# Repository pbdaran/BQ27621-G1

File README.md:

# BQ27621 Arduino Library

This Arduino library provides a comprehensive interface for the Texas Instruments BQ27621-G1 battery fuel gauge IC, enabling easy integration with Arduino-based projects. The library supports all major features of the BQ27621-G1 as described in the Technical Reference Manual (SLUUAD4C, December 2013 - Revised August 2014).

## Features

- **Control Commands**: Manage device states (SEALED/UNSEALED, CONFIG UPDATE, SHUTDOWN, etc.).
- **Standard Commands**: Read battery parameters such as Temperature, Voltage, StateOfCharge, RemainingCapacity, and more.
- **Extended Commands**: Access and modify Operation Configuration, Design Capacity, and block data operations.
- **Data Memory Access**: Configure safety parameters, charge termination, SOC thresholds, sleep current, terminate voltage, and battery chemistry ID.
- **Battery Profile Selection**: Support for default (CHEM_ID 0x1202) and alternate chemistry profiles (0x1210 for 4.3V, 0x354 for 4.35V).
- **I2C Communication**: Robust functions for reading and writing word and block data over I2C.

## Requirements

- **Hardware**:
  - Arduino-compatible board with I2C support (e.g., Arduino Uno, Mega, etc.).
  - BQ27621-G1 battery fuel gauge IC connected via I2C (SDA, SCL, power lines).
- **Software**:
  - Arduino IDE (version 1.8.0 or later recommended).
  - Wire library (included with Arduino IDE).
- **Dependencies**: None beyond the standard Arduino Wire library.

## Installation

1. **Download the Library**:
   - Clone this repository or download the ZIP file.
   - Extract the `BQ27621` folder containing `BQ27621.h`, `BQ27621.cpp`, and the example sketch.

2. **Install the Library**:
   - Place the `BQ27621` folder in your Arduino `libraries` directory (typically `~/Arduino/libraries/`).
   - Restart the Arduino IDE if it was open during installation.

3. **Connect the Hardware**:
   - Connect the BQ27621-G1 to your Arduino:
     - SDA to Arduino SDA pin.
     - SCL to Arduino SCL pin.
     - VCC to 3.3V or 5V (check your board's compatibility).
     - GND to Arduino GND.
   - Verify the I2C address (default: 0x55). Adjust in the constructor if different.

4. **Open the Example**:
   - In the Arduino IDE, go to `File > Examples > BQ27621 > BQ27621_Example`.
   - Upload the example sketch to your Arduino.

## Usage

The library provides a `BQ27621` class with methods to interact with the fuel gauge. Below is a basic example of initializing the device and reading battery parameters:

```cpp
#include <Wire.h>
#include "BQ27621.h"

BQ27621 batteryGauge; // Default I2C address: 0x55

void setup() {
    Serial.begin(9600);
    while (!Serial);

    if (!batteryGauge.begin()) {
        Serial.println("Failed to initialize BQ27621!");
        while (1);
    }
    Serial.println("BQ27621 Initialized Successfully");

    // Configure battery parameters
    batteryGauge.setUnsealed();
    batteryGauge.enterConfigUpdate();
    batteryGauge.setDesignCapacity(1200); // Set to 1200mAh
    batteryGauge.setTerminateVoltage(3200); // Set to 3200mV
    batteryGauge.exitConfigUpdate();
    batteryGauge.setSealed();
}

void loop() {
    Serial.print("Voltage: ");
    Serial.print(batteryGauge.getVoltage());
    Serial.println(" mV");

    Serial.print("State of Charge: ");
    Serial.print(batteryGauge.getStateOfCharge());
    Serial.println(" %");

    Serial.print("Remaining Capacity: ");
    Serial.print(batteryGauge.getRemainingCapacity());
    Serial.println(" mAh");

    delay(5000); // Update every 5 seconds
}
```

## Example Sketch

The provided example sketch (`BQ27621_Example.ino`) demonstrates the full range of library features, including:

- Initializing the BQ27621-G1 and verifying communication.
- Configuring the device in UNSEALED mode.
- Setting safety parameters, charge termination, SOC thresholds, and operation configurations.
- Selecting an alternate battery chemistry profile (e.g., CHEM_ID 0x1210 for 4.3V batteries).
- Reading and displaying battery status (voltage, SOC, capacity, current, power, etc.).
- Toggling the GPOUT pin for debugging.

To use the example:
1. Open `BQ27621_Example.ino` in the Arduino IDE.
2. Adjust configuration parameters (e.g., DesignCapacity, TerminateVoltage) based on your battery specifications.
3. Upload the sketch and monitor the Serial output at 9600 baud.

## Library Methods

### Constructor
- `BQ27621(uint8_t i2cAddress = 0x55)`: Initialize with the I2C address (default: 0x55).

### Initialization
- `bool begin()`: Initialize I2C communication and verify device presence.

### Control Commands
- `uint16_t getControlStatus()`: Read the control status register.
- `void setBatteryInsert()`: Signal battery insertion.
- `void setBatteryRemove()`: Signal battery removal.
- `void enterShutdown()`: Enter SHUTDOWN mode.
- `void setSealed()`: Transition to SEALED mode.
- `void setUnsealed()`: Transition to UNSEALED mode (using default keys 0x8000 0x8000).
- `void toggleGPOUT()`: Pulse the GPOUT pin for 1ms.
- `void selectAltChem1()`: Select CHEM_ID 0x1210 (4.3V).
- `void selectAltChem2()`: Select CHEM_ID 0x354 (4.35V).
- `void enterConfigUpdate()`: Enter CONFIG UPDATE mode.
- `void exitConfigUpdate()`: Exit CONFIG UPDATE without OCV measurement.
- `void exitResim()`: Exit CONFIG UPDATE with resimulation.

### Standard Commands
- `uint16_t getTemperature()`: Read temperature in 0.1K.
- `void setTemperature(uint16_t temp)`: Set temperature (if OpConfig[TEMPS] = 1).
- `uint16_t getVoltage()`: Read cell voltage in mV.
- `uint16_t getFlags()`: Read status flags.
- `uint16_t getNominalAvailableCapacity()`: Read uncompensated capacity in mAh.
- `uint16_t getFullAvailableCapacity()`: Read uncompensated full capacity in mAh.
- `uint16_t getRemainingCapacity()`: Read compensated remaining capacity in mAh.
- `uint16_t getFullChargeCapacity()`: Read compensated full capacity in mAh.
- `int16_t getEffectiveCurrent()`: Read estimated current in mA.
- `int16_t getAveragePower()`: Read average power in mW.
- `uint16_t getStateOfCharge()`: Read state of charge in %.
- `uint16_t getInternalTemperature()`: Read internal temperature in 0.1K.
- `uint16_t getRemainingCapacityUnfiltered()`: Read unfiltered remaining capacity in mAh.
- `uint16_t getRemainingCapacityFiltered()`: Read filtered remaining capacity in mAh.
- `uint16_t getFullChargeCapacityUnfiltered()`: Read unfiltered full capacity in mAh.
- `uint16_t getFullChargeCapacityFiltered()`: Read filtered full capacity in mAh.
- `uint16_t getStateOfChargeUnfiltered()`: Read unfiltered state of charge in %.

### Extended Commands
- `uint16_t getOpConfig()`: Read operation configuration.
- `uint16_t getDesignCapacity()`: Read design capacity in mAh.
- `void setDesignCapacity(uint16_t capacity)`: Set design capacity.
- `uint8_t getBlockDataChecksum()`: Read block data checksum.
- `void setBlockDataChecksum(uint8_t checksum)`: Set block data checksum.
- `void setBlockDataControl(uint8_t value)`: Control data access mode.
- `void selectDataClass(uint8_t classId)`: Select data memory class.
- `void selectDataBlock(uint8_t blockId)`: Select data block.
- `void writeBlockData(uint8_t offset, uint8_t* data, uint8_t len)`: Write block data.
- `void readBlockData(uint8_t offset, uint8_t* data, uint8_t len)`: Read block data.

### Data Memory Configuration
- `void setSafetyParameters(uint16_t ot, uint16_t ut, uint8_t tHysteresis)`: Set over-temperature, under-temperature, and hysteresis.
- `void setChargeTerminationParameters(uint16_t minTaperCap, uint8_t taperWindow, int8_t fcSet, uint8_t fcClear)`: Set charge termination parameters.
- `void setSOCThresholds(uint8_t socfSet, uint8_t socfClear)`: Set SOC final discharge thresholds.
- `void setOpConfig(uint16_t config)`: Set operation configuration.
- `void setOpConfigB(uint8_t config)`: Set operation configuration B.
- `void setSleepCurrent(uint16_t current)`: Set sleep current threshold.
- `void setTerminateVoltage(uint16_t voltage)`: Set terminate voltage.
- `void setChemID(uint16_t chemId)`: Set chemistry ID.

## Notes

- **I2C Address**: The default I2C address is 0x55. If your BQ27621-G1 uses a different address, specify it in the constructor.
- **SEALED vs. UNSEALED Mode**: Configuration changes require UNSEALED mode. The library uses the default unseal keys (0x8000 0x8000). For production, set the device to SEALED mode after configuration.
- **Battery Chemistry**: The library supports switching between three chemistry profiles (0x1202, 0x1210, 0x354). Ensure the selected profile matches your battery's maximum charging voltage (4.2V, 4.3V, or 4.35V).
- **Power Modes**: The BQ27621-G1 automatically manages power modes (NORMAL, SLEEP, HIBERNATE, SHUTDOWN). Use `enterShutdown()` carefully, as it requires a GPOUT pin transition to wake up.
- **Error Handling**: The `begin()` function checks for device presence. Always verify initialization before proceeding.
- **Checksums**: Block data operations include automatic checksum calculation to ensure data integrity.

## Troubleshooting

- **No Communication**: Verify I2C connections, pull-up resistors (4.7kΩ recommended), and the correct I2C address.
- **Invalid Readings**: Ensure the device is properly configured (e.g., correct chemistry ID, design capacity). Check if the device is in SEALED mode, which restricts some operations.
- **Configuration Issues**: Enter UNSEALED mode before making configuration changes. Use `enterConfigUpdate()` for data memory modifications.

## License

This library is released under the MIT License. See the `LICENSE` file for details.

## Acknowledgments

- Based on the Texas Instruments BQ27621-G1 Technical Reference Manual (SLUUAD4C).
- Developed for use with Arduino-compatible platforms.

For further details, refer to the BQ27621-G1 datasheet (SLUSB3) and Quick Start Guide (SLUUAP5) available at [www.ti.com](http://www.ti.com).

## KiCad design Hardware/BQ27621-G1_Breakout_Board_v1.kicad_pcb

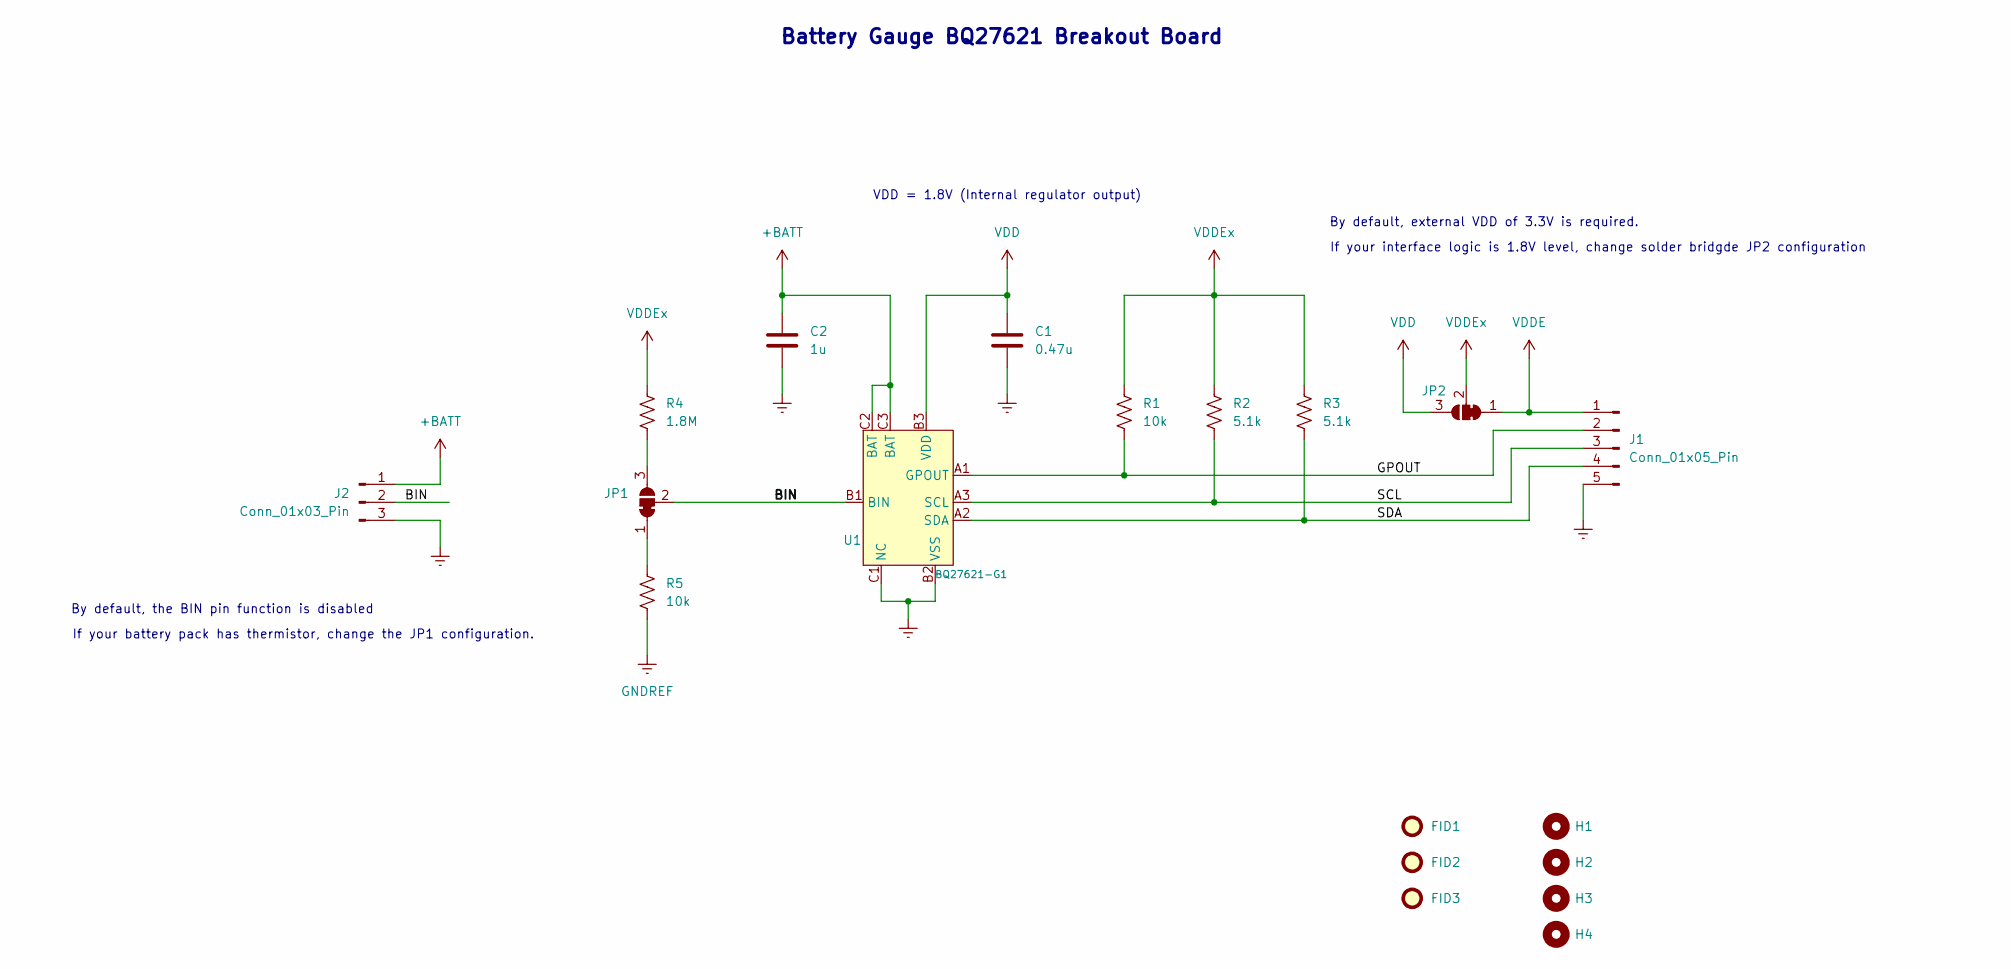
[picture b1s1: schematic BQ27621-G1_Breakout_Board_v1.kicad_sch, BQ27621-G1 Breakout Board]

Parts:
C1: 0.47u; C_0603_1608Metric_Pad1.08x0.95mm_HandSolder; MPN UMK107B7474KA-TR
C2: 1u; C_0603_1608Metric_Pad1.08x0.95mm_HandSolder; MPN CL10B105KO8NNNC
FID1, FID2, FID3: Fiducial; Fiducial_0.5mm_Mask1mm
H1, H2, H3, H4: MountingHole; MountingHole_2.2mm_M2
J1: Conn_01x05_Pin; PinHeader_1x05_P2.54mm_Vertical; MPN 61300511121
J2: Conn_01x03_Pin; PinHeader_1x03_P2.54mm_Vertical; MPN G800W305018EU
JP1, JP2: SolderJumper_3_Bridged12; SolderJumper-3_P1.3mm_Bridged12_Pad1.0x1.5mm
R1, R5: 10k; R_0603_1608Metric_Pad0.98x0.95mm_HandSolder; MPN RMCF0603FT10K0
R2, R3: 5.1k; R_0603_1608Metric_Pad0.98x0.95mm_HandSolder; MPN RMCF0603FT5K10
R4: 1.8M; R_0603_1608Metric_Pad0.98x0.95mm_HandSolder; MPN RC0603FR-071M8L
U1: BQ27621-G1; Texas_DSBGA-9_1.62x1.58mm_Layout3x3_P0.5mm; MPN BQ27621YZFR-G1A

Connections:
+BATT: C2.1, J2.1, U1.C2 (BAT), U1.C3 (BAT)
/BIN: J2.2, JP1.2 (C), U1.B1 (BIN)
/GPOUT: J1.2, R1.2, U1.A1 (GPOUT)
/SCL: J1.3, R2.2, U1.A3 (SCL)
/SDA: J1.4, R3.2, U1.A2 (SDA)
GNDREF: C1.2, C2.2, J1.5, J2.3, R5.2, U1.B2 (VSS), U1.C1 (NC)
unnamed: JP1.1 (A), R5.1
unnamed: JP1.3 (B), R4.2
VDD: C1.1, JP2.3 (B), U1.B3 (VDD)
VDDE: J1.1, JP2.1 (A)
VDDEx: JP2.2 (C), R1.1, R2.1, R3.1, R4.1

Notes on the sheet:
If your battery pack has thermistor, change the JP1 configuration.
By default, the BIN pin function is disabled
VDD = 1.8V (Internal regulator output)
If your interface logic is 1.8V level, change solder bridgde JP2 configuration
Battery Gauge BQ27621 Breakout Board
By default, external VDD of 3.3V is required.

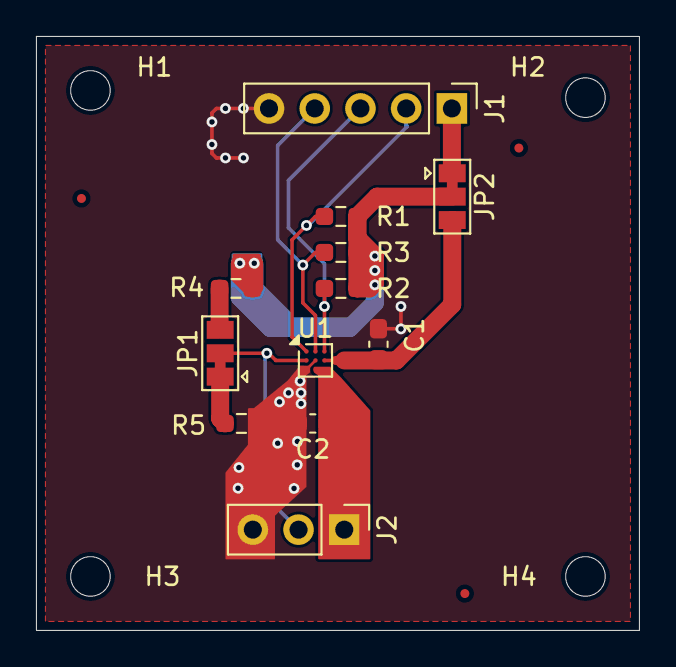
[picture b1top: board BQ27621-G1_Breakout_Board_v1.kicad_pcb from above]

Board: 2 copper layers, 33.5 x 33.0 mm, 19 parts (0 on the bottom side), 11 nets.

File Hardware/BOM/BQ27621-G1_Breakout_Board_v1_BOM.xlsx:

S.No. | Reference Designator | Qty | Value | Manufacturer PartName | Manufacturer | Description
1 | > R2, R3 | 2 | 5.1k | RMCF0603FT5K10 | Stackpole Electronics Inc | RES 5.1K OHM 1% 1/10W 0603
2 | > R1, R5 | 2 | 10k | RMCF0603FT10K0 | Stackpole Electronics Inc | RES 10K OHM 1% 1/10W 0603
3 | U1 | 1 | BQ27621-G1 | BQ27621YZFR-G1A | Texas Instruments | IC BATT FUEL GAUGE LIION 9DSBGA
4 | R4 | 1 | 1.8M | RC0603FR-071M8L | YAGEO | RES 1.8M OHM 1% 1/10W 0603
5 | J2 | 1 | Conn_01x03_Pin | G800W305018EU | Amphenol ICC (Commercial Products) | PIN HEADER 2.54MM PITCH STR,1X3P
6 | J1 | 1 | Conn_01x05_Pin | 61300511121 | Würth Elektronik | CONN HEADER VERT 5POS 2.54MM
7 | C2 | 1 | 1u | CL10B105KO8NNNC | Samsung Electro-Mechanics | CAP CER 1UF 16V X7R 0603
8 | C1 | 1 | 0.47u | UMK107B7474KA-TR | Taiyo Yuden | CAP CER 0.47UF 50V X7R 0603

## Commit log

2025-08-02 Update BQ27621.h
    Summary of changes/fixes:
    ALT_CHEM1/2 control subcommands: Use 0x0031 and 0x0032 as per TRM.
    enterConfigUpdate: Uses proper SET_CFGUPDATE (0x0013).
    Block Data writes: All Data Flash updates now read the full 32-byte block, modify only the targeted fields, recalculate the checksum for the entire block, and write back the entire block. This avoids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
    setDesignCapacity: Implements both (a) debug (volatile RAM, not persistent, via extended command) and (b) permanent (via Data Flash memory) update, based on a boolean parameter.
    Rich comments throughout.
2025-08-02 Update BQ27621.cpp
    Summary of changes/fixes:
    ALT_CHEM1/2 control subcommands: Use 0x0031 and 0x0032 as per TRM.
    enterConfigUpdate: Uses proper SET_CFGUPDATE (0x0013).
    Block Data writes: All Data Flash updates now read the full 32-byte block, modify only the targeted fields, recalculate the checksum for the entire block, and write back the entire block. This avoids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
    setDesignCapacity: Implements both (a) debug (volatile RAM, not persistent, via extended command) and (b) permanent (via Data Flash memory) update, based on a boolean parameter.
    Rich comments throughout.
2025-08-02 Update BQ27621_Example.ino
    Revised according to new driver file.
2025-08-02 Update LICENSE
    ## License
    This project is licensed under the [MIT License](./LICENSE).
